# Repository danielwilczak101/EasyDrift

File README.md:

# EasyDrift
1. Trying to make a crazy cart be able to drive and drift using an A.I
2. Make a python package to make vechiles driveable easy for everyone else.
#### Current Progress
https://www.youtube.com/watch?v=hL62QS8LPps

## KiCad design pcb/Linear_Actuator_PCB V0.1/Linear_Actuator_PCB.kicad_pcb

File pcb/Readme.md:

This is the Autonomous Cart PCB folder

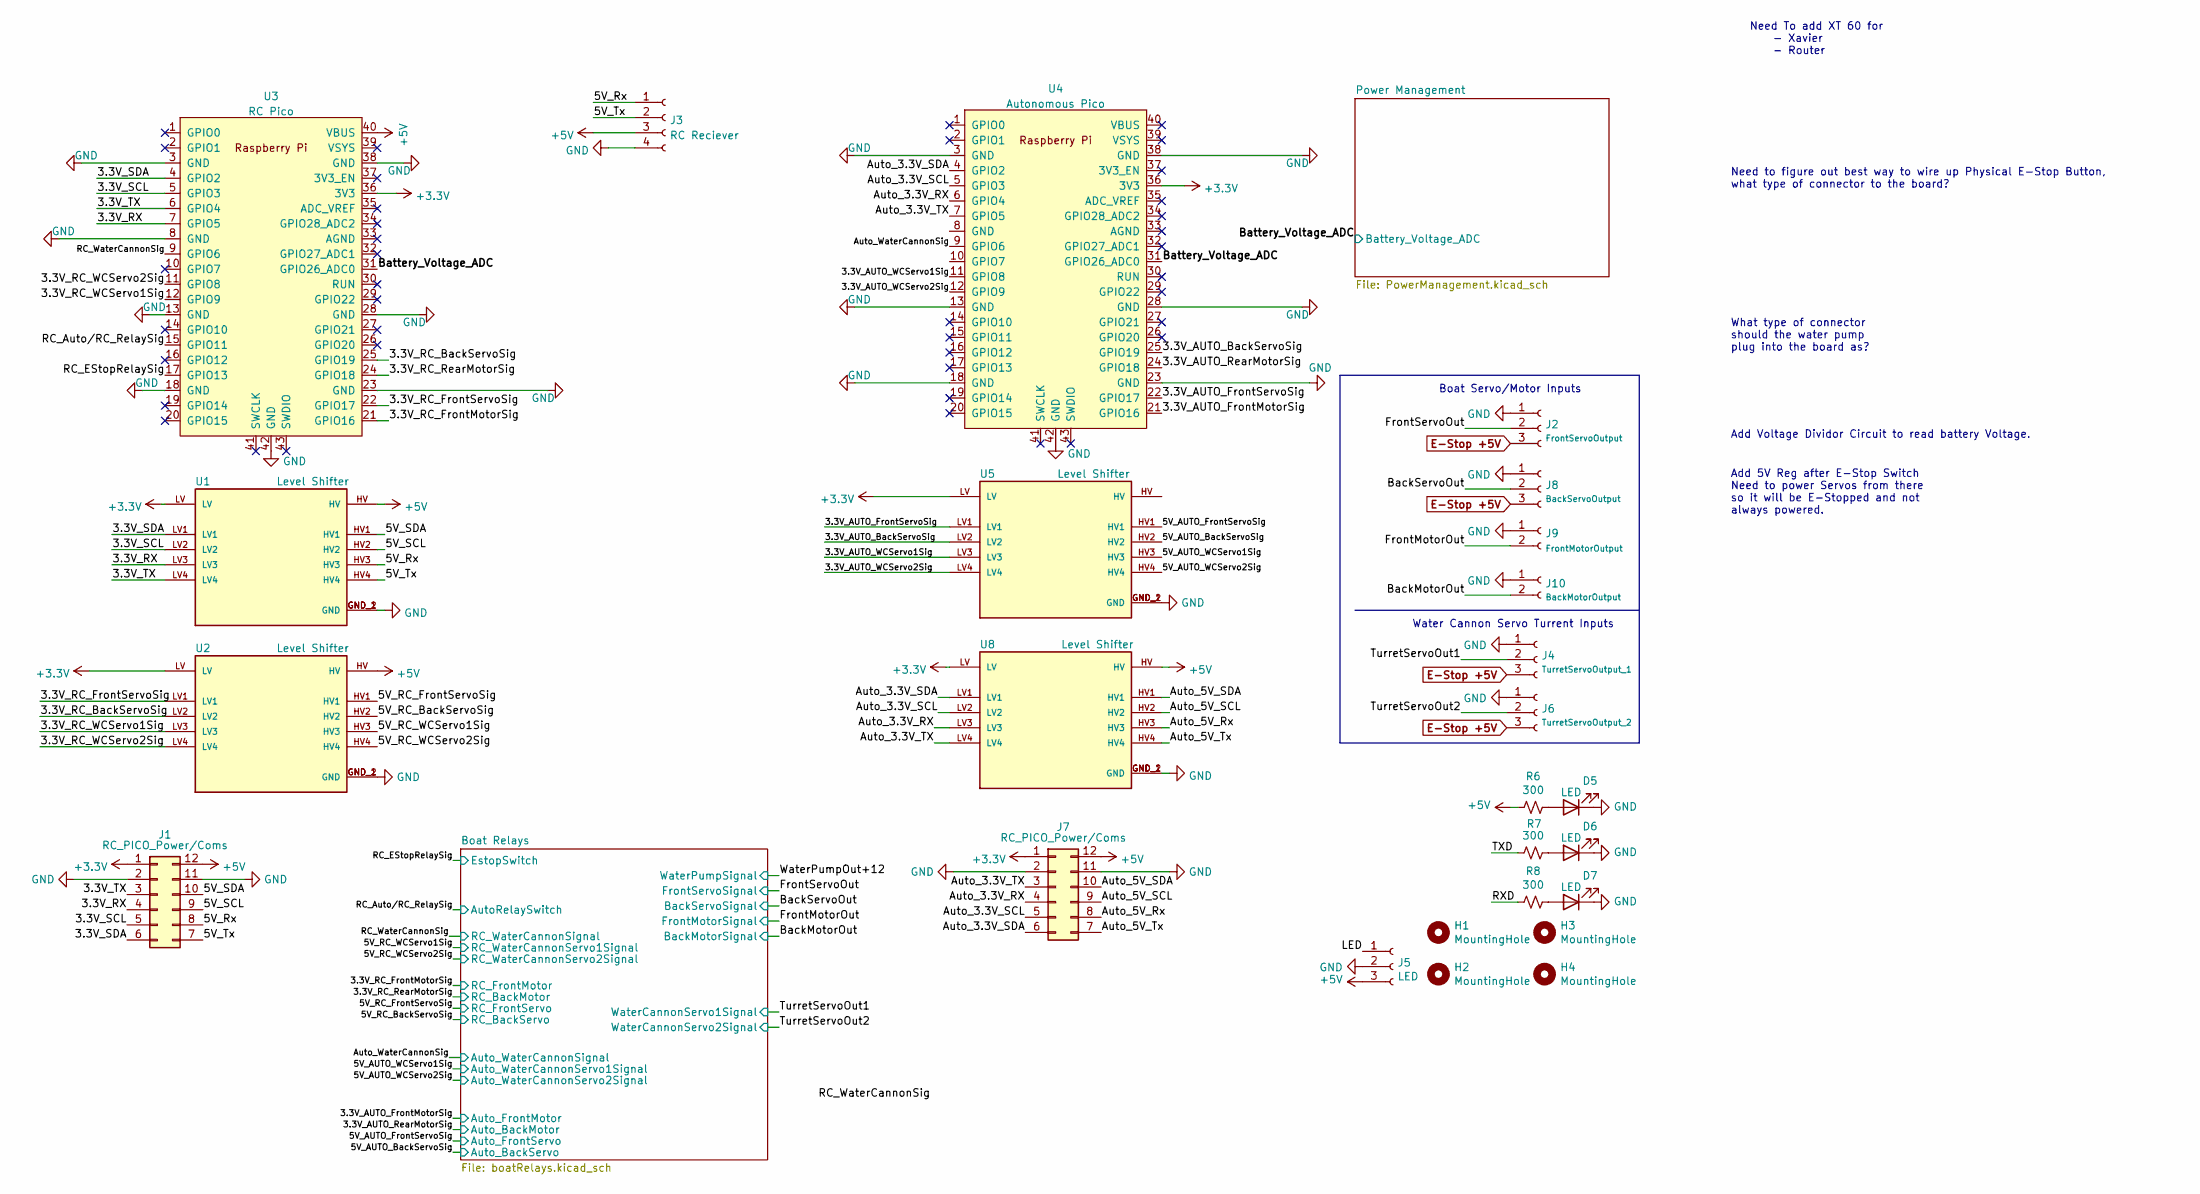
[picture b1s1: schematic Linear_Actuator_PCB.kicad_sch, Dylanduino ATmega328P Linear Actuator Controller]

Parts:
D5, D6, D7: LED; LED_0402_1005Metric
H1, H2, H3, H4: MountingHole; MountingHole_5.3mm_M5
J1: RC_PICO_Power/Coms; PinSocket_2x06_P2.54mm_Vertical_SMD
J2: FrontServoOutput; PinHeader_1x03_P2.54mm_Vertical
J3: RC Reciever; PinHeader_1x04_P2.54mm_Vertical
J4: TurretServoOutput_1; PinHeader_1x03_P2.54mm_Vertical
J5: LED; PinHeader_1x03_P2.54mm_Vertical
J6: TurretServoOutput_2; PinHeader_1x03_P2.54mm_Vertical
J7: RC_PICO_Power/Coms; PinSocket_2x06_P2.54mm_Vertical
J8: BackServoOutput; PinHeader_1x03_P2.54mm_Vertical
J9: FrontMotorOutput; PinSocket_2x06_P2.54mm_Vertical
J10: BackMotorOutput; PinSocket_2x06_P2.54mm_Vertical
R6, R7, R8: 300; R_0603_1608Metric
U1, U2, U5, U8: Level Shifter; CONV_BOB-12009; PARTREV 01
U3: RC Pico; RPi_Pico_SMD_TH
U4: Autonomous Pico; RPi_Pico_SMD_TH

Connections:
+3V3: J1.1, J7.1, U1.LV, U2.LV, U3.36 (3V3), U4.36 (3V3), U5.LV, U8.LV
+5V: J1.12, J3.3, J5.3, J7.12, R6.2, U1.HV, U2.HV, U3.40 (VBUS), U8.HV; also elsewhere on the board
/3.3V_AUTO_BackServoSig: U4.25 (GPIO19), U5.LV2
/3.3V_AUTO_FrontMotorSig: U4.21 (GPIO16); also elsewhere on the board
/3.3V_AUTO_FrontServoSig: U4.22 (GPIO17), U5.LV1
/3.3V_AUTO_RearMotorSig: U4.24 (GPIO18); also elsewhere on the board
/3.3V_AUTO_WCServo1Sig: U4.11 (GPIO8), U5.LV3
/3.3V_AUTO_WCServo2Sig: U4.12 (GPIO9), U5.LV4
/3.3V_RC_BackServoSig: U2.LV2, U3.25 (GPIO19)
/3.3V_RC_FrontMotorSig: U3.21 (GPIO16); also elsewhere on the board
/3.3V_RC_FrontServoSig: U2.LV1, U3.22 (GPIO17)
/3.3V_RC_RearMotorSig: U3.24 (GPIO18); also elsewhere on the board
/3.3V_RC_WCServo1Sig: U2.LV3, U3.12 (GPIO9)
/3.3V_RC_WCServo2Sig: U2.LV4, U3.11 (GPIO8)
/3.3V_RX: J1.4, U1.LV3, U3.7 (GPIO5)
/3.3V_SCL: J1.5, U1.LV2, U3.5 (GPIO3)
/3.3V_SDA: J1.6, U1.LV1, U3.4 (GPIO2)
/3.3V_TX: J1.3, U1.LV4, U3.6 (GPIO4)
/5V_AUTO_BackServoSig: U5.HV2; also elsewhere on the board
/5V_AUTO_FrontServoSig: U5.HV1; also elsewhere on the board
/5V_AUTO_WCServo1Sig: U5.HV3; also elsewhere on the board
/5V_AUTO_WCServo2Sig: U5.HV4; also elsewhere on the board
/5V_RC_BackServoSig: U2.HV2; also elsewhere on the board
/5V_RC_FrontServoSig: U2.HV1; also elsewhere on the board
/5V_RC_WCServo1Sig: U2.HV3; also elsewhere on the board
/5V_RC_WCServo2Sig: U2.HV4; also elsewhere on the board
/5V_Rx: J1.8, J3.1, U1.HV3
/5V_SCL: J1.9, U1.HV2
/5V_SDA: J1.10, U1.HV1
/5V_Tx: J1.7, J3.2, U1.HV4
/Auto_3.3V_RX: J7.4, U4.6 (GPIO4), U8.LV3
/Auto_3.3V_SCL: J7.5, U4.5 (GPIO3), U8.LV2
/Auto_3.3V_SDA: J7.6, U4.4 (GPIO2), U8.LV1
/Auto_3.3V_TX: J7.3, U4.7 (GPIO5), U8.LV4
/Auto_5V_Rx: J7.8, U8.HV3
/Auto_5V_SCL: J7.9, U8.HV2
/Auto_5V_SDA: J7.10, U8.HV1
/Auto_5V_Tx: J7.7, U8.HV4
/Auto_WaterCannonSig: U4.9 (GPIO6); also elsewhere on the board
/BackMotorOut: J10.2; also elsewhere on the board
/BackServoOut: J8.2; also elsewhere on the board
/Battery_Voltage_ADC: U3.31 (GPIO26_ADC0), U4.31 (GPIO26_ADC0); also elsewhere on the board
/FrontMotorOut: J9.2; also elsewhere on the board
/FrontServoOut: J2.2; also elsewhere on the board
/LED: J5.1
/RC_Auto/RC_RelaySig: U3.15 (GPIO11); also elsewhere on the board
/RC_EStopRelaySig: U3.17 (GPIO13); also elsewhere on the board
/RC_WaterCannonSig: U3.9 (GPIO6); also elsewhere on the board
/RXD: R8.2
/TXD: R7.2
/TurretServoOut1: J4.2; also elsewhere on the board
/TurretServoOut2: J6.2; also elsewhere on the board
E-Stop +5V: J2.3, J4.3, J6.3, J8.3; also elsewhere on the board
unnamed: D5.2 (A), R6.1
unnamed: D6.2 (A), R7.1
unnamed: D7.2 (A), R8.1

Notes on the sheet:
Need To add XT 60 for - Xavier - Router
Add Voltage Dividor Circuit to read battery Voltage.
Need to figure out best way to wire up Physical E-Stop Button, what type of connector to the board?
Boat Servo/Motor Inputs
What type of connector should the water pump plug into the board as?
Water Cannon Servo Turrent Inputs
Add 5V Reg after E-Stop Switch Need to power Servos from there so it will be E-Stopped and not always powered.

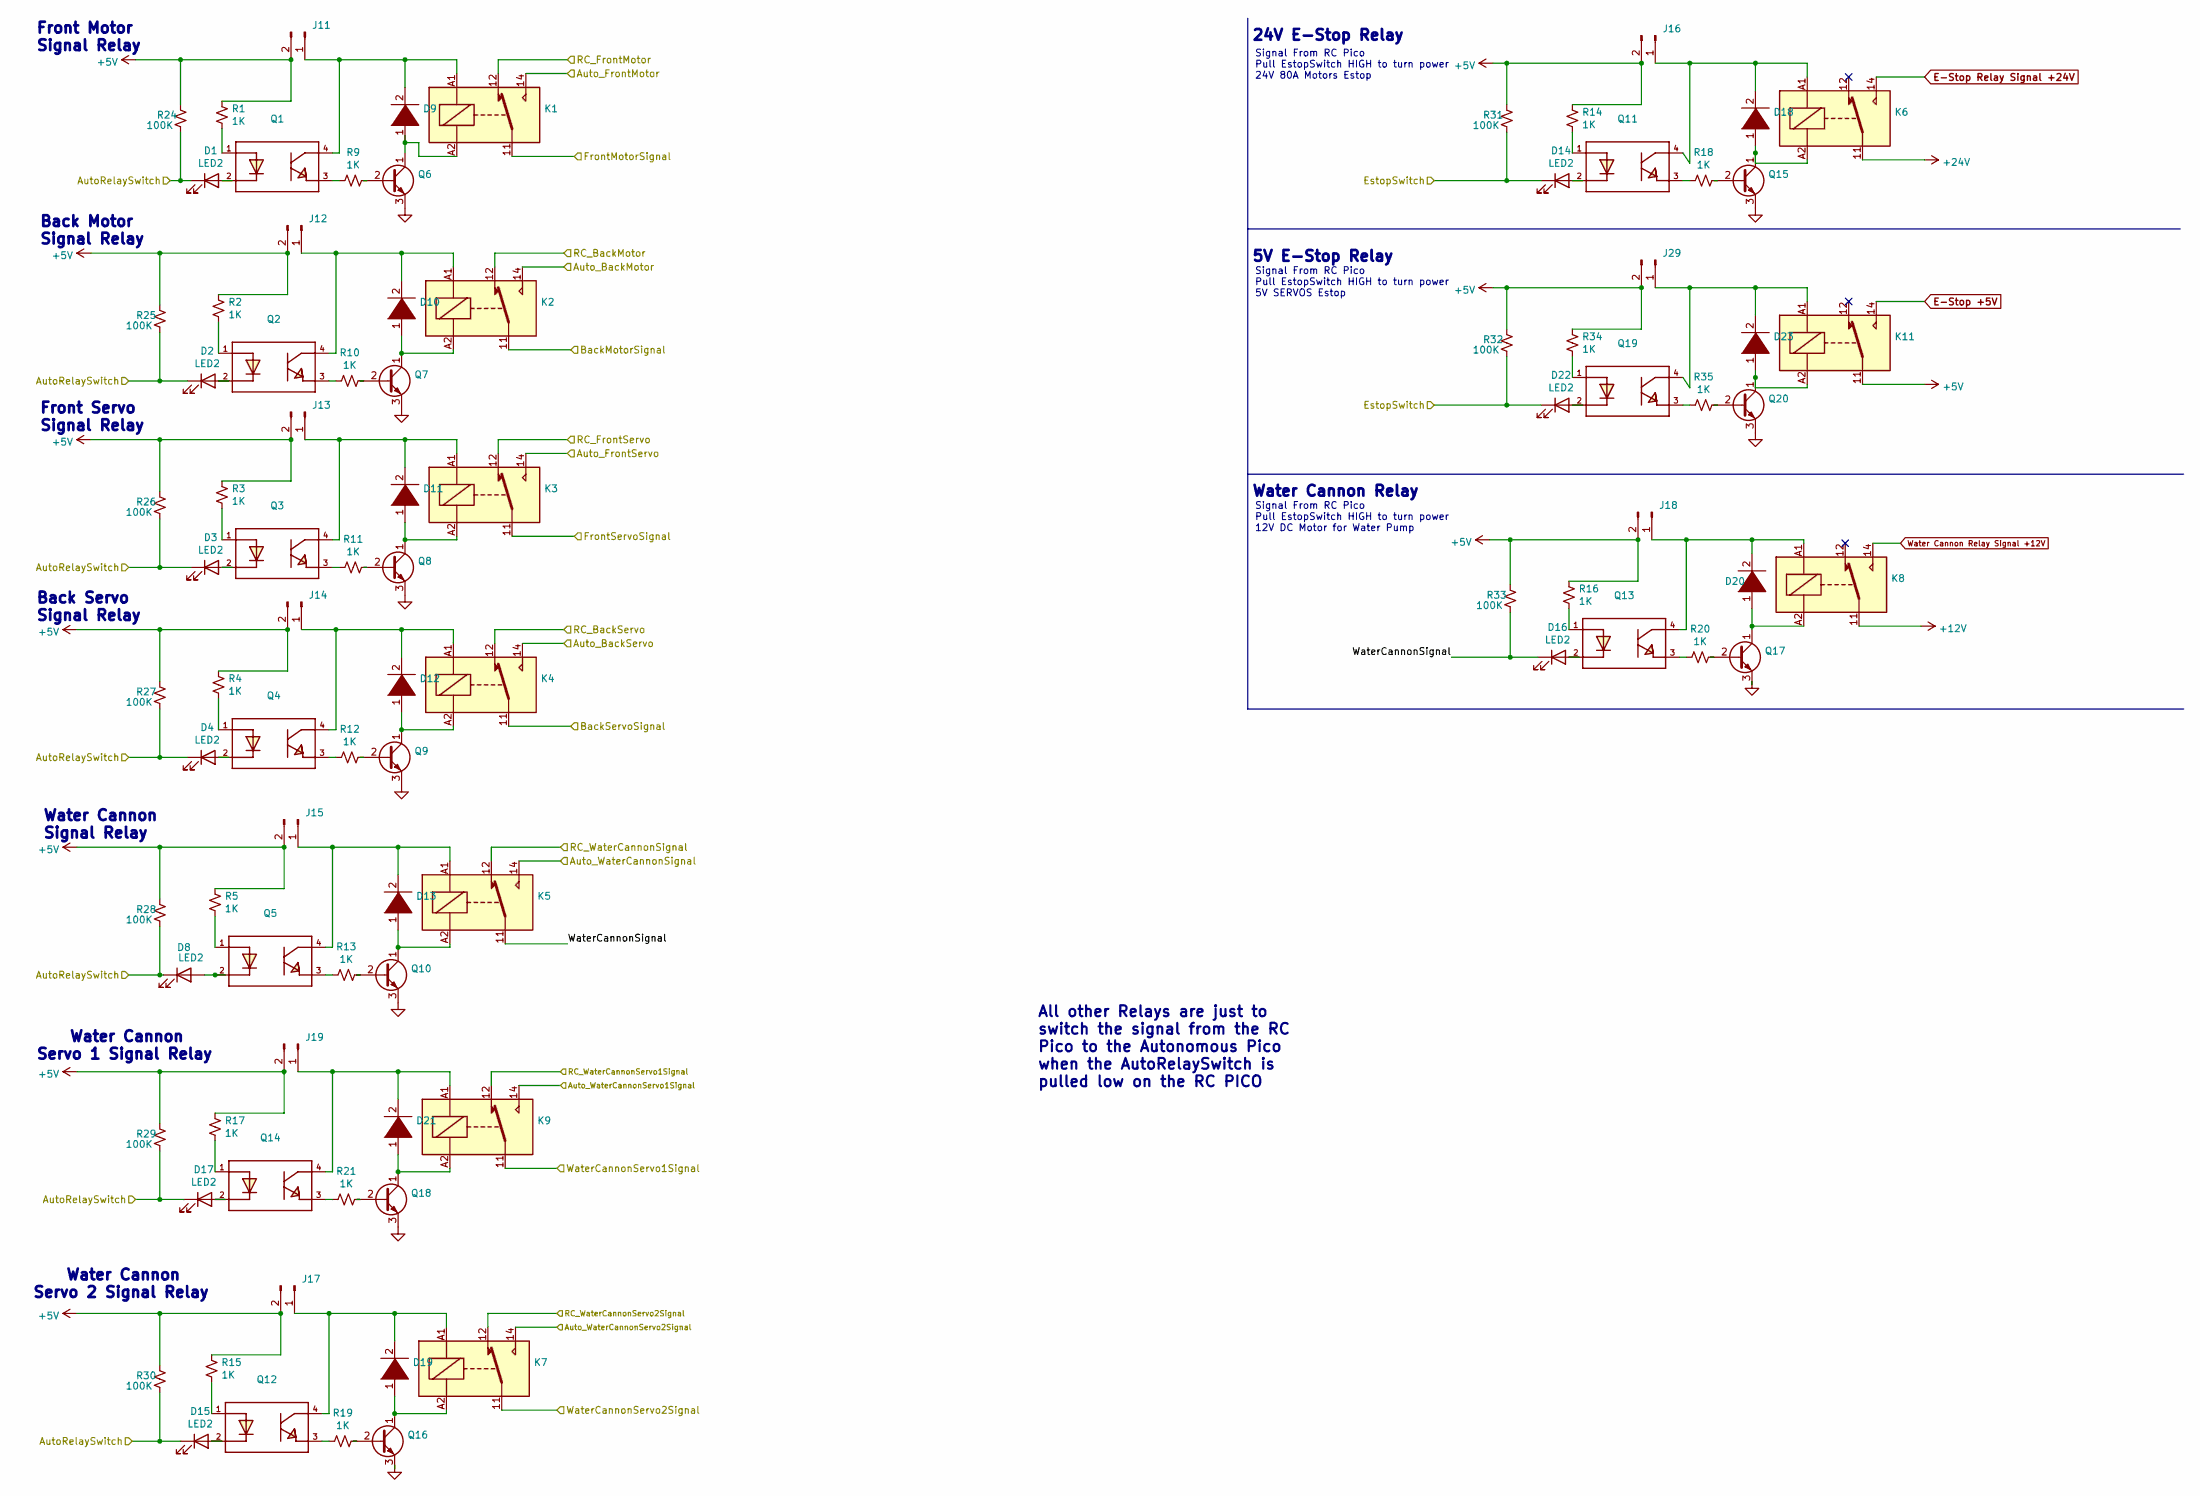
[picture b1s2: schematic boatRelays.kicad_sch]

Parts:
D1, D2, D3, D4, D8, D14, D15, D16, D17, D22: LED2; LED_0402_1005Metric
D9, D10, D11, D12, D13, D18, D19, D20, D21, D23: D_1210_3225Metric
J11, J12, J13, J14, J15, J16, J17, J18, J19, J29: PinHeader_1x02_P2.54mm_Vertical
K1, K2, K3, K4, K5, K6, K7, K8, K9, K11: Relay_SPDT_Finder_36.11
Q1, Q2, Q3, Q4, Q5, Q11, Q12, Q13, Q14, Q19: DIP762W50P254L650H458Q4B
Q6, Q7, Q8, Q9, Q10, Q15, Q16, Q17, Q18, Q20: TO-92_Inline
R1, R2, R3, R4, R5, R9, R10, R11, R12, R13, R14, R15, R16, R17, R18, R19, R20, R21, R34, R35: 1K; R_0805_2012Metric
R24, R25, R26, R27, R28, R29, R30, R31, R32, R33: 100K; R_0805_2012Metric

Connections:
+5V: J11.2, J12.2, J13.2, J14.2, J15.2, J16.2, J17.2, J18.2, J19.2, J29.2, K11.11, R1.1, R2.1, R3.1, R4.1, R5.1, R14.1, R15.1, R16.1, R17.1, R24.1, R25.1, R26.1, R27.1, R28.1, R29.1, R30.1, R31.1, R32.1, R33.1, R34.1; also elsewhere on the board
+12V: K8.11; also elsewhere on the board
+24V: K6.11; also elsewhere on the board
/3.3V_AUTO_FrontMotorSig: K1.14; also elsewhere on the board
/3.3V_AUTO_RearMotorSig: K2.14; also elsewhere on the board
/3.3V_RC_FrontMotorSig: K1.12; also elsewhere on the board
/3.3V_RC_RearMotorSig: K2.12; also elsewhere on the board
/5V_AUTO_BackServoSig: K4.14; also elsewhere on the board
/5V_AUTO_FrontServoSig: K3.14; also elsewhere on the board
/5V_AUTO_WCServo1Sig: K9.14; also elsewhere on the board
/5V_AUTO_WCServo2Sig: K7.14; also elsewhere on the board
/5V_RC_BackServoSig: K4.12; also elsewhere on the board
/5V_RC_FrontServoSig: K3.12; also elsewhere on the board
/5V_RC_WCServo1Sig: K9.12; also elsewhere on the board
/5V_RC_WCServo2Sig: K7.12; also elsewhere on the board
/Auto_WaterCannonSig: K5.14; also elsewhere on the board
/BackMotorOut: K2.11; also elsewhere on the board
/BackServoOut: K4.11; also elsewhere on the board
/Boat Relays/WaterCannonSignal: D16.1 (K), K5.11, R33.2
/FrontMotorOut: K1.11; also elsewhere on the board
/FrontServoOut: K3.11; also elsewhere on the board
/RC_Auto/RC_RelaySig: D1.1 (K), D2.1 (K), D3.1 (K), D4.1 (K), D8.1 (K), D15.1 (K), D17.1 (K), R24.2, R25.2, R26.2, R27.2, R28.2, R29.2, R30.2; also elsewhere on the board
/RC_EStopRelaySig: D14.1 (K), D22.1 (K), R31.2, R32.2; also elsewhere on the board
/RC_WaterCannonSig: K5.12; also elsewhere on the board
/TurretServoOut1: K9.11; also elsewhere on the board
/TurretServoOut2: K7.11; also elsewhere on the board
E-Stop +5V: K11.14; also elsewhere on the board
E-Stop Relay Signal +24V: K6.14
unnamed: D1.2 (A), Q1.2
unnamed: D2.2 (A), Q2.2
unnamed: D3.2 (A), Q3.2
unnamed: D4.2 (A), Q4.2
unnamed: D8.2 (A), Q5.2
unnamed: D9.1 (K), K1.A2, Q6.1 (C)
unnamed: D9.2 (A), J11.1, K1.A1, Q1.4
unnamed: D10.1 (K), K2.A2, Q7.1 (C)
unnamed: D10.2 (A), J12.1, K2.A1, Q2.4
unnamed: D11.1 (K), K3.A2, Q8.1 (C)
unnamed: D11.2 (A), J13.1, K3.A1, Q3.4
unnamed: D12.1 (K), K4.A2, Q9.1 (C)
unnamed: D12.2 (A), J14.1, K4.A1, Q4.4
unnamed: D13.1 (K), K5.A2, Q10.1 (C)
unnamed: D13.2 (A), J15.1, K5.A1, Q5.4
unnamed: D14.2 (A), Q11.2
unnamed: D15.2 (A), Q12.2
unnamed: D16.2 (A), Q13.2
unnamed: D17.2 (A), Q14.2
unnamed: D18.1 (K), K6.A2, Q15.1 (C)
unnamed: D18.2 (A), J16.1, K6.A1, Q11.4
unnamed: D19.1 (K), K7.A2, Q16.1 (C)
unnamed: D19.2 (A), J17.1, K7.A1, Q12.4
unnamed: D20.1 (K), K8.A2, Q17.1 (C)
unnamed: D20.2 (A), J18.1, K8.A1, Q13.4
unnamed: D21.1 (K), K9.A2, Q18.1 (C)
unnamed: D21.2 (A), J19.1, K9.A1, Q14.4
unnamed: D22.2 (A), Q19.2
unnamed: D23.1 (K), K11.A2, Q20.1 (C)
unnamed: D23.2 (A), J29.1, K11.A1, Q19.4
unnamed: Q1.1, R1.2
unnamed: Q1.3, R9.2
unnamed: Q2.1, R2.2
unnamed: Q2.3, R10.2
unnamed: Q3.1, R3.2
unnamed: Q3.3, R11.2
unnamed: Q4.1, R4.2
unnamed: Q4.3, R12.2
unnamed: Q5.1, R5.2
unnamed: Q5.3, R13.2
unnamed: Q6.2 (B), R9.1
unnamed: Q7.2 (B), R10.1
unnamed: Q8.2 (B), R11.1
unnamed: Q9.2 (B), R12.1
unnamed: Q10.2 (B), R13.1
unnamed: Q11.1, R14.2
unnamed: Q11.3, R18.2
unnamed: Q12.1, R15.2
unnamed: Q12.3, R19.2
unnamed: Q13.1, R16.2
unnamed: Q13.3, R20.2
unnamed: Q14.1, R17.2
unnamed: Q14.3, R21.2
unnamed: Q15.2 (B), R18.1
unnamed: Q16.2 (B), R19.1
unnamed: Q17.2 (B), R20.1
unnamed: Q18.2 (B), R21.1
unnamed: Q19.1, R34.2
unnamed: Q19.3, R35.2
unnamed: Q20.2 (B), R35.1
Water Cannon Relay Signal +12V: K8.14; also elsewhere on the board

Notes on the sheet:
5V E-Stop Relay
All other Relays are just to switch the signal from the RC Pico to the Autonomous Pico when the AutoRelaySwitch is pulled low on the RC PICO
Front Motor Signal Relay
Water Cannon Servo 1 Signal Relay
Water Cannon Servo 2 Signal Relay
Front Servo Signal Relay
Signal From RC Pico Pull EstopSwitch HIGH to turn power 5V SERVOS Estop
24V E-Stop Relay
Back Motor Signal Relay
Water Cannon Relay
Back Servo Signal Relay
Water Cannon Signal Relay
Signal From RC Pico Pull EstopSwitch HIGH to turn power 24V 80A Motors Estop
Signal From RC Pico Pull EstopSwitch HIGH to turn power 12V DC Motor for Water Pump

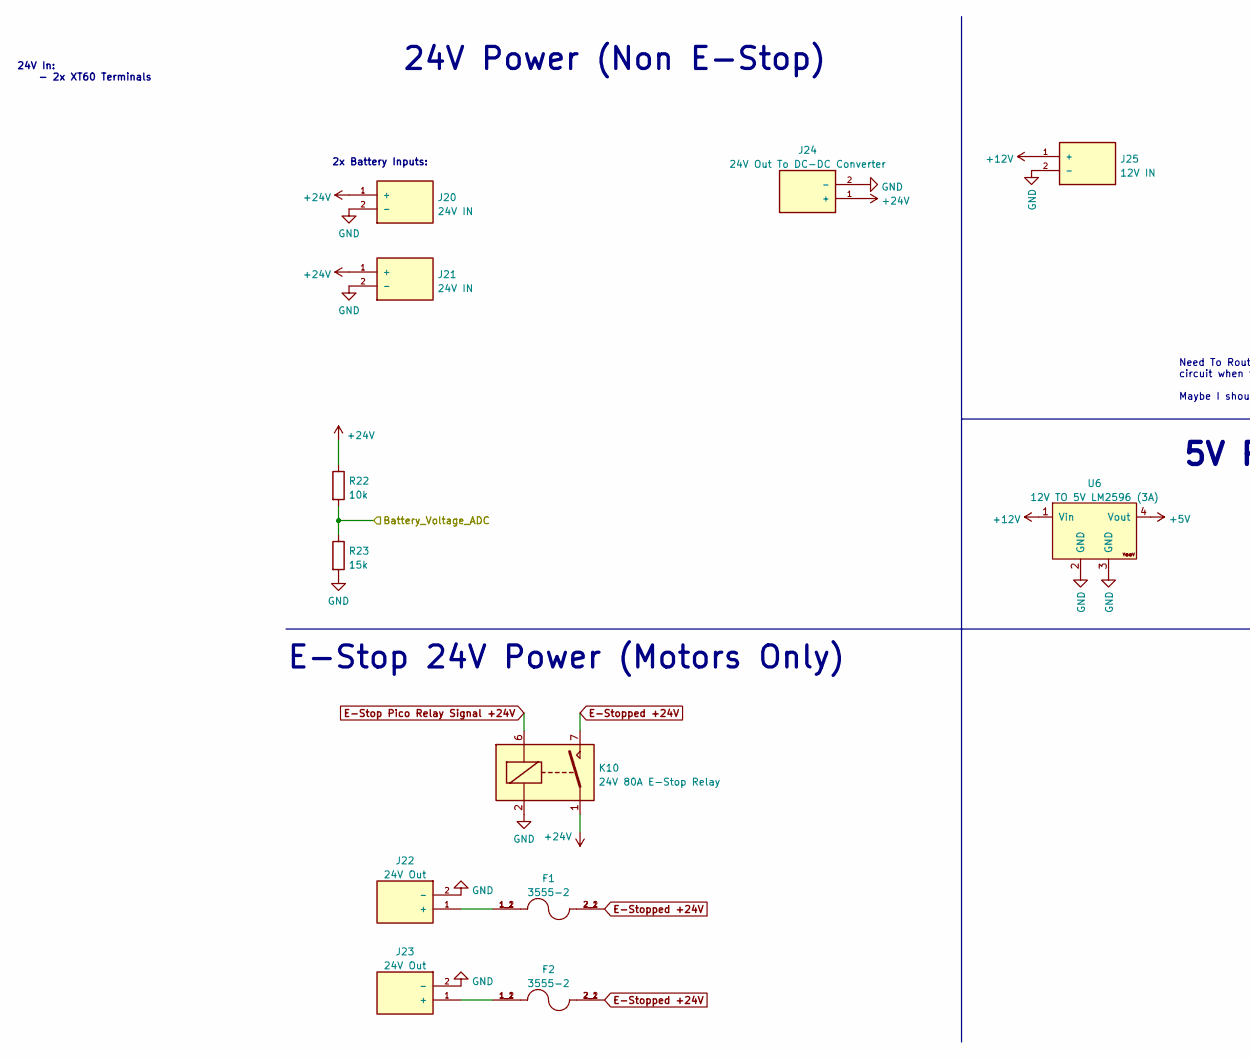
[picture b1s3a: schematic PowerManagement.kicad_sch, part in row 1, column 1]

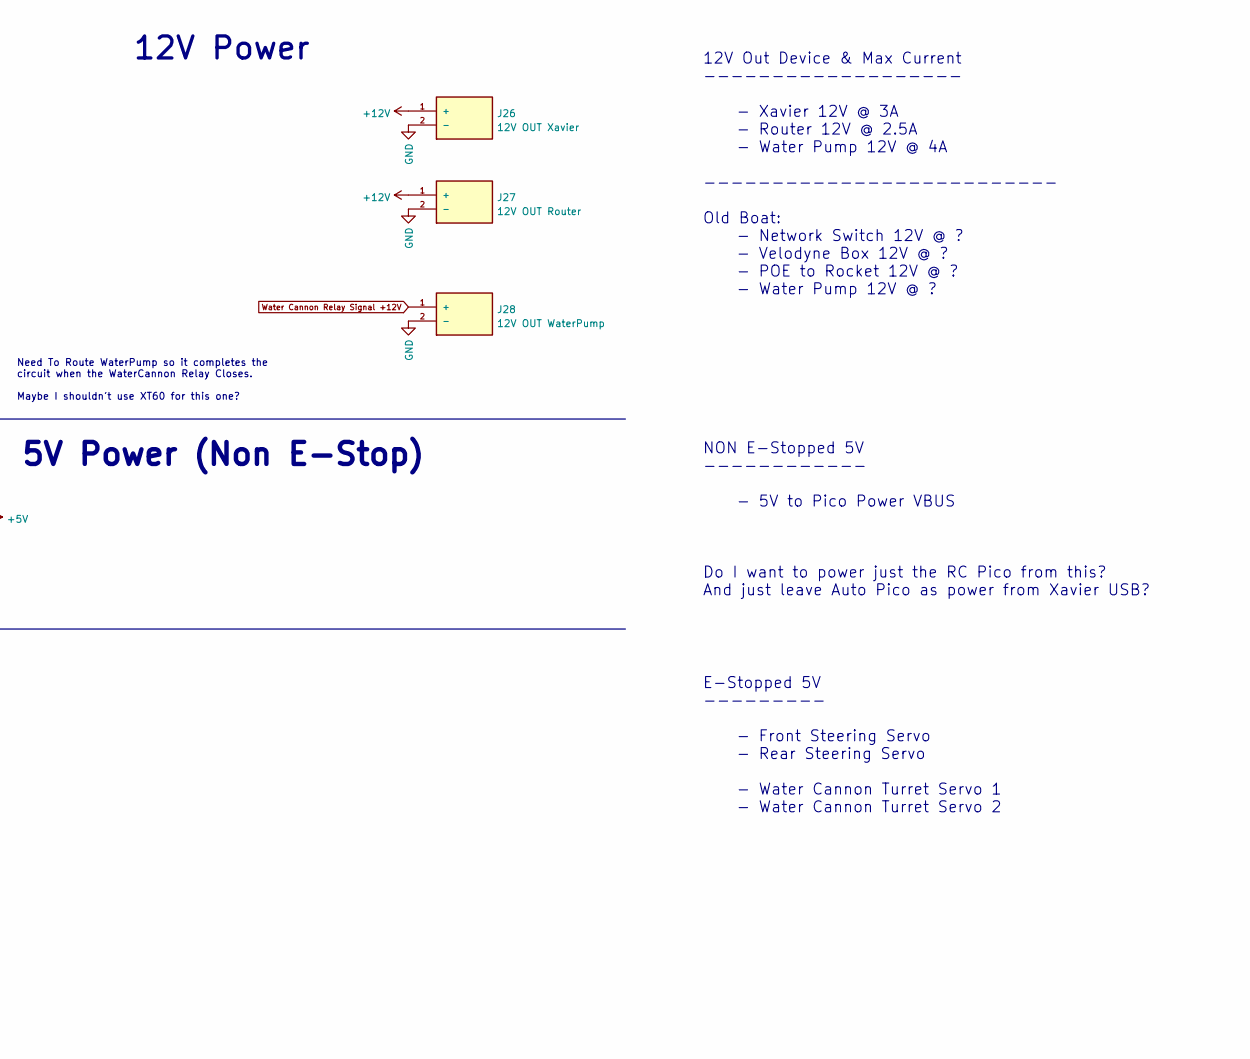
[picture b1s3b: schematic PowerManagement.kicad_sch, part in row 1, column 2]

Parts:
F1, F2: 3555-2; FUSE_3555-2; PARTREV A
J20, J21: 24V IN; AMASS_XT60PW-M; PARTREV V1.2
J22, J23: 24V Out; AMASS_XT60PW-M; PARTREV V1.2
J24: 24V Out To DC-DC Converter; AMASS_XT60PW-M; PARTREV V1.2
J25: 12V IN; AMASS_XT60PW-M; PARTREV V1.2
J26: 12V OUT Xavier; AMASS_XT60PW-M; PARTREV V1.2
J27: 12V OUT Router; AMASS_XT60PW-M; PARTREV V1.2
J28: 12V OUT WaterPump; AMASS_XT60PW-M; PARTREV V1.2
K10: 24V 80A E-Stop Relay; JD2912-1H-24VDC 80A 28VDC
R22: 10k; R_0805_2012Metric
R23: 15k; R_0805_2012Metric
U6: 12V TO 5V LM2596 (3A); DCDC_StepDown_LM2596

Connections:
+5V: U6.4 (Vout); also elsewhere on the board
+12V: J25.1 (+), J26.1 (+), J27.1 (+), U6.1 (Vin); also elsewhere on the board
+24V: J20.1 (+), J21.1 (+), J24.1 (+), K10.1, K10.14, R22.1; also elsewhere on the board
/Battery_Voltage_ADC: R22.2, R23.1; also elsewhere on the board
E-Stopped +24V: F1.2_1, F1.2_2, F2.2_1, F2.2_2, K10.7, K10.8
unnamed: F1.1_1, F1.1_2, J22.1 (+)
unnamed: F2.1_1, F2.1_2, J23.1 (+)
Water Cannon Relay Signal +12V: J28.1 (+); also elsewhere on the board

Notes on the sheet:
12V Out Device & Max Current ------------------- - Xavier 12V @ 3A - Router 12V @ 2.5A - Water Pump 12V @ 4A -------------------------- Old Boat: - Network Switch 12V @ ? - Velodyne Box 12V @ ? - POE to Rocket 12V @ ? - Water Pump 12V @ ?
24V Power (Non E-Stop)
2x Battery Inputs:
12V Power
Need To Route WaterPump so it completes the circuit when the WaterCannon Relay Closes. Maybe I shouldn't use XT60 for this one?
24V In: - 2x XT60 Terminals
NON E-Stopped 5V ------------ - 5V to Pico Power VBUS Do I want to power just the RC Pico from this? And just leave Auto Pico as power from Xavier USB?
E-Stop 24V Power (Motors Only)
E-Stopped 5V --------- - Front Steering Servo - Rear Steering Servo - Water Cannon Turret Servo 1 - Water Cannon Turret Servo 2
5V Power (Non E-Stop)

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
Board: 2 copper layers, 131 parts (0 on the bottom side), 121 nets, no tracks yet.

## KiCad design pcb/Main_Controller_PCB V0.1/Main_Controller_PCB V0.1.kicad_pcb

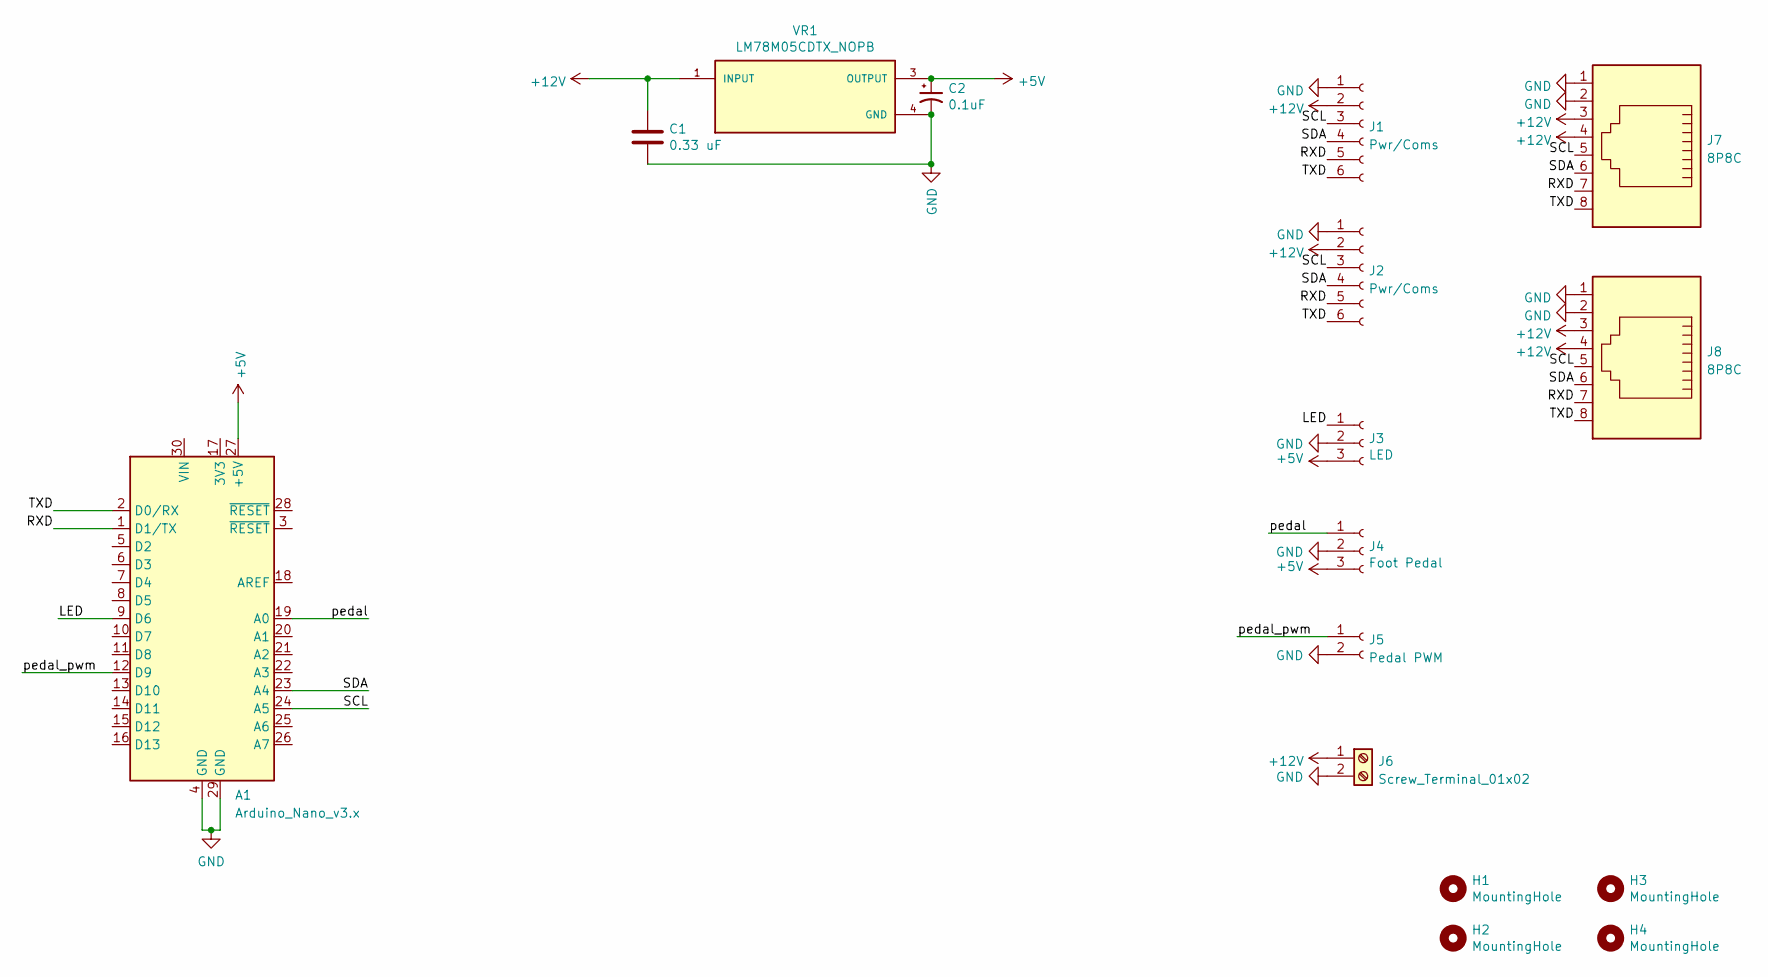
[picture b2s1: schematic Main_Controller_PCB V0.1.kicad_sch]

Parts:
A1: Arduino_Nano_v3.x; Arduino_Nano
C1: 0.33 uF; C_0603_1608Metric
C2: 0.1uF; C_0603_1608Metric
H1, H2, H3, H4: MountingHole; MountingHole_2.2mm_M2
J1, J2: Pwr/Coms; PinHeader_1x06_P2.54mm_Vertical
J3: LED; PinHeader_1x03_P2.54mm_Vertical
J4: Foot Pedal; PinHeader_1x03_P2.54mm_Vertical
J5: Pedal PWM; PinHeader_1x02_P2.54mm_Vertical
J6: Screw_Terminal_01x02; TE_282837-2
J7, J8: 8P8C; RJ45_Ninigi_GE
VR1: LM78M05CDTX_NOPB; TO228P991X255-3N; PARTREV G

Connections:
+5V: A1.27 (+5V), C2.1, J3.3, J4.3, VR1.3 (OUTPUT)
+12V: C1.1, J1.2, J2.2, J6.1, J7.3, J7.4, J8.3, J8.4, VR1.1 (INPUT)
/LED: A1.9 (D6), J3.1
/RXD: A1.1 (D1/TX), J1.5, J2.5, J7.7, J8.7
/SCL: A1.24 (A5), J1.3, J2.3, J7.5, J8.5
/SDA: A1.23 (A4), J1.4, J2.4, J7.6, J8.6
/TXD: A1.2 (D0/RX), J1.6, J2.6, J7.8, J8.8
/pedal: A1.19 (A0), J4.1
/pedal_pwm: A1.12 (D9), J5.1
GND: A1.4 (GND), A1.29 (GND), C1.2, C2.2, J1.1, J2.1, J3.2, J4.2, J5.2, J6.2, J7.1, J7.2, J8.1, J8.2, VR1.4 (GND)

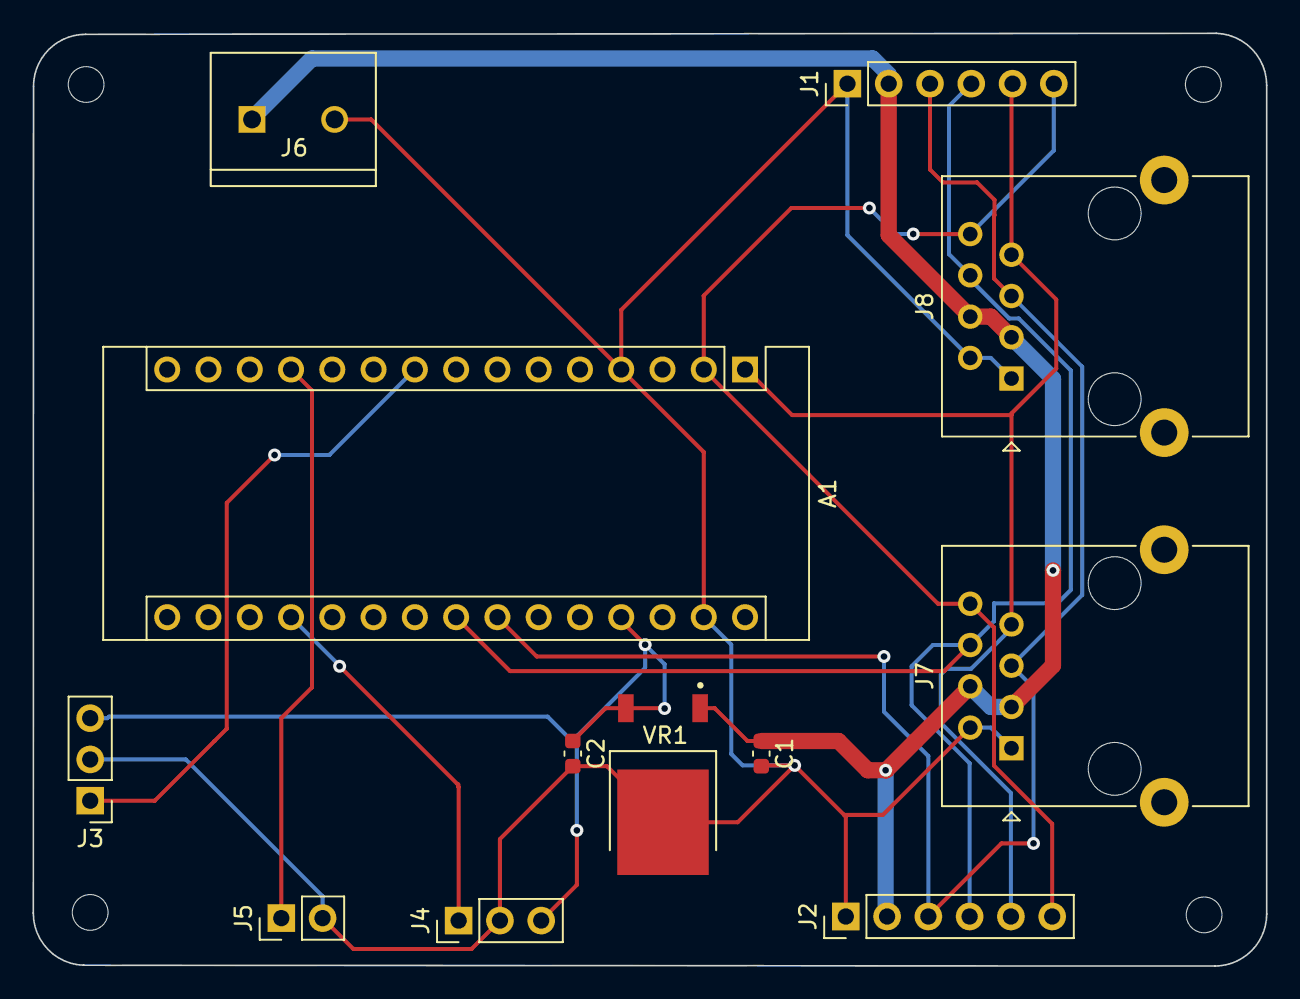
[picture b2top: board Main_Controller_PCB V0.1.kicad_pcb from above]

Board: 2 copper layers, 75.9 x 57.4 mm, 16 parts (0 on the bottom side), 10 nets.

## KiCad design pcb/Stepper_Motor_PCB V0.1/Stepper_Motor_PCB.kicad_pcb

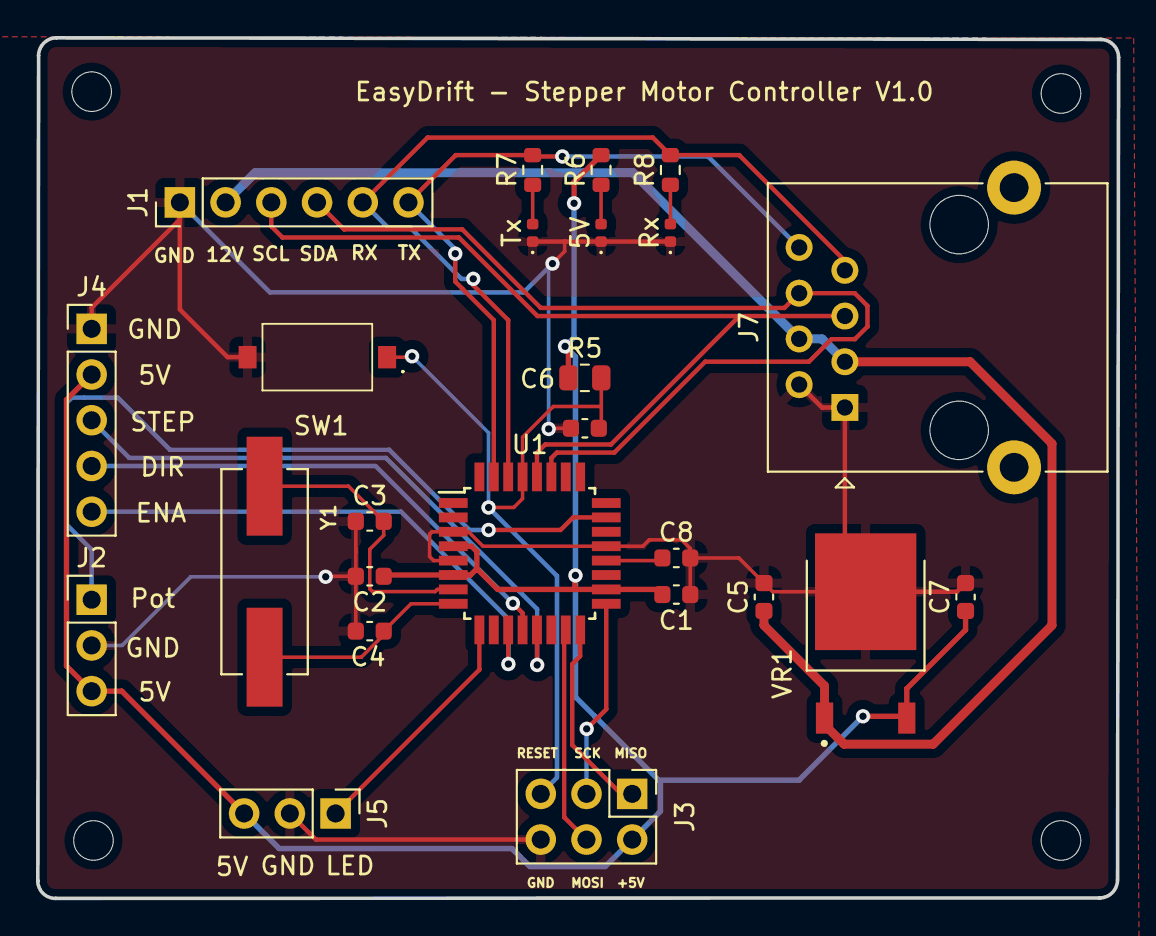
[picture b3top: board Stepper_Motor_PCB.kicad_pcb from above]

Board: 2 copper layers, 60.0 x 47.8 mm, 29 parts (0 on the bottom side), 22 nets.

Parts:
5V: LED; LED_0402_1005Metric
C1, C2, C6, C8: 100nF; C_0603_1608Metric
C3, C4: 22pf; C_0603_1608Metric
C5: 0.33 uF; C_0603_1608Metric
C7: 0.1uF; C_0603_1608Metric
H1, H2, H3, H4: MountingHole; MountingHole_2.2mm_M2
J1: Pwr/Coms; PinHeader_1x06_P2.54mm_Vertical
J2: Pot; PinHeader_1x03_P2.54mm_Vertical
J3: Bootloader Pins; PinHeader_2x03_P2.54mm_Vertical
J4: Stepper_Motor; PinHeader_1x05_P2.54mm_Vertical
J5: LED; PinHeader_1x03_P2.54mm_Vertical
J7: 8P8C; RJ45_Ninigi_GE
R5: 10k; R_0805_2012Metric
R6, R7, R8: 300; R_0603_1608Metric
Rx: LED; LED_0402_1005Metric
SW1: SW_Push; PTS636SK25SMTRLFS
Tx: LED; LED_0402_1005Metric
U1: ATmega328P-AU; TQFP-32_7x7mm_P0.8mm
VR1: LM78M05CDTX_NOPB; TO228P991X255-3N
Y1: Crystal; XTAL_ECS-160-20-5PXDN-TR

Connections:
+5V: C1.2, C2.1, C7.1, J2.3, J3.2, J4.2, J5.3, R5.1, R6.2, U1.4 (VCC), U1.6 (VCC), U1.18 (AVCC), VR1.3 (OUTPUT)
+12V: C5.1, J1.2, J7.3, J7.4, VR1.1 (INPUT)
/Dir: J4.4, U1.12 (PB0)
/Enable: J4.5, U1.11 (PD7)
/LED: J5.1, U1.9 (PD5)
/MISO: J3.1, U1.16 (PB4)
/MOSI: J3.4, U1.15 (PB3)
/RXD: J1.5, J7.7, R8.2, U1.30 (PD0)
/Reset: C6.2, J3.5, R5.2, SW1.1, U1.29 (~RESET/PC6)
/SCK: J3.3, U1.17 (PB5)
/SCL: J1.3, J7.5, U1.28 (PC5)
/SDA: J1.4, J7.6, U1.27 (PC4)
/Step: J4.3, U1.13 (PB1)
/TXD: J1.6, J7.8, R7.2, U1.31 (PD1)
/pot: J2.1, U1.23 (PC0)
GND: 5V.1 (K), C1.1, C2.2, C3.1, C4.1, C5.2, C6.1, C7.2, C8.2, J1.1, J2.2, J3.6, J4.1, J5.2, J7.1, J7.2, Rx.1 (K), SW1.2, Tx.1 (K), U1.3 (GND), U1.5 (GND), U1.21 (GND), VR1.4 (GND)
unnamed: C3.2, U1.7 (XTAL1/PB6), Y1.1
unnamed: C4.2, U1.8 (XTAL2/PB7), Y1.2
unnamed: 5V.2 (A), R6.1
unnamed: R7.1, Tx.2 (A)
unnamed: R8.1, Rx.2 (A)
unnamed: C8.1, U1.20 (AREF)
